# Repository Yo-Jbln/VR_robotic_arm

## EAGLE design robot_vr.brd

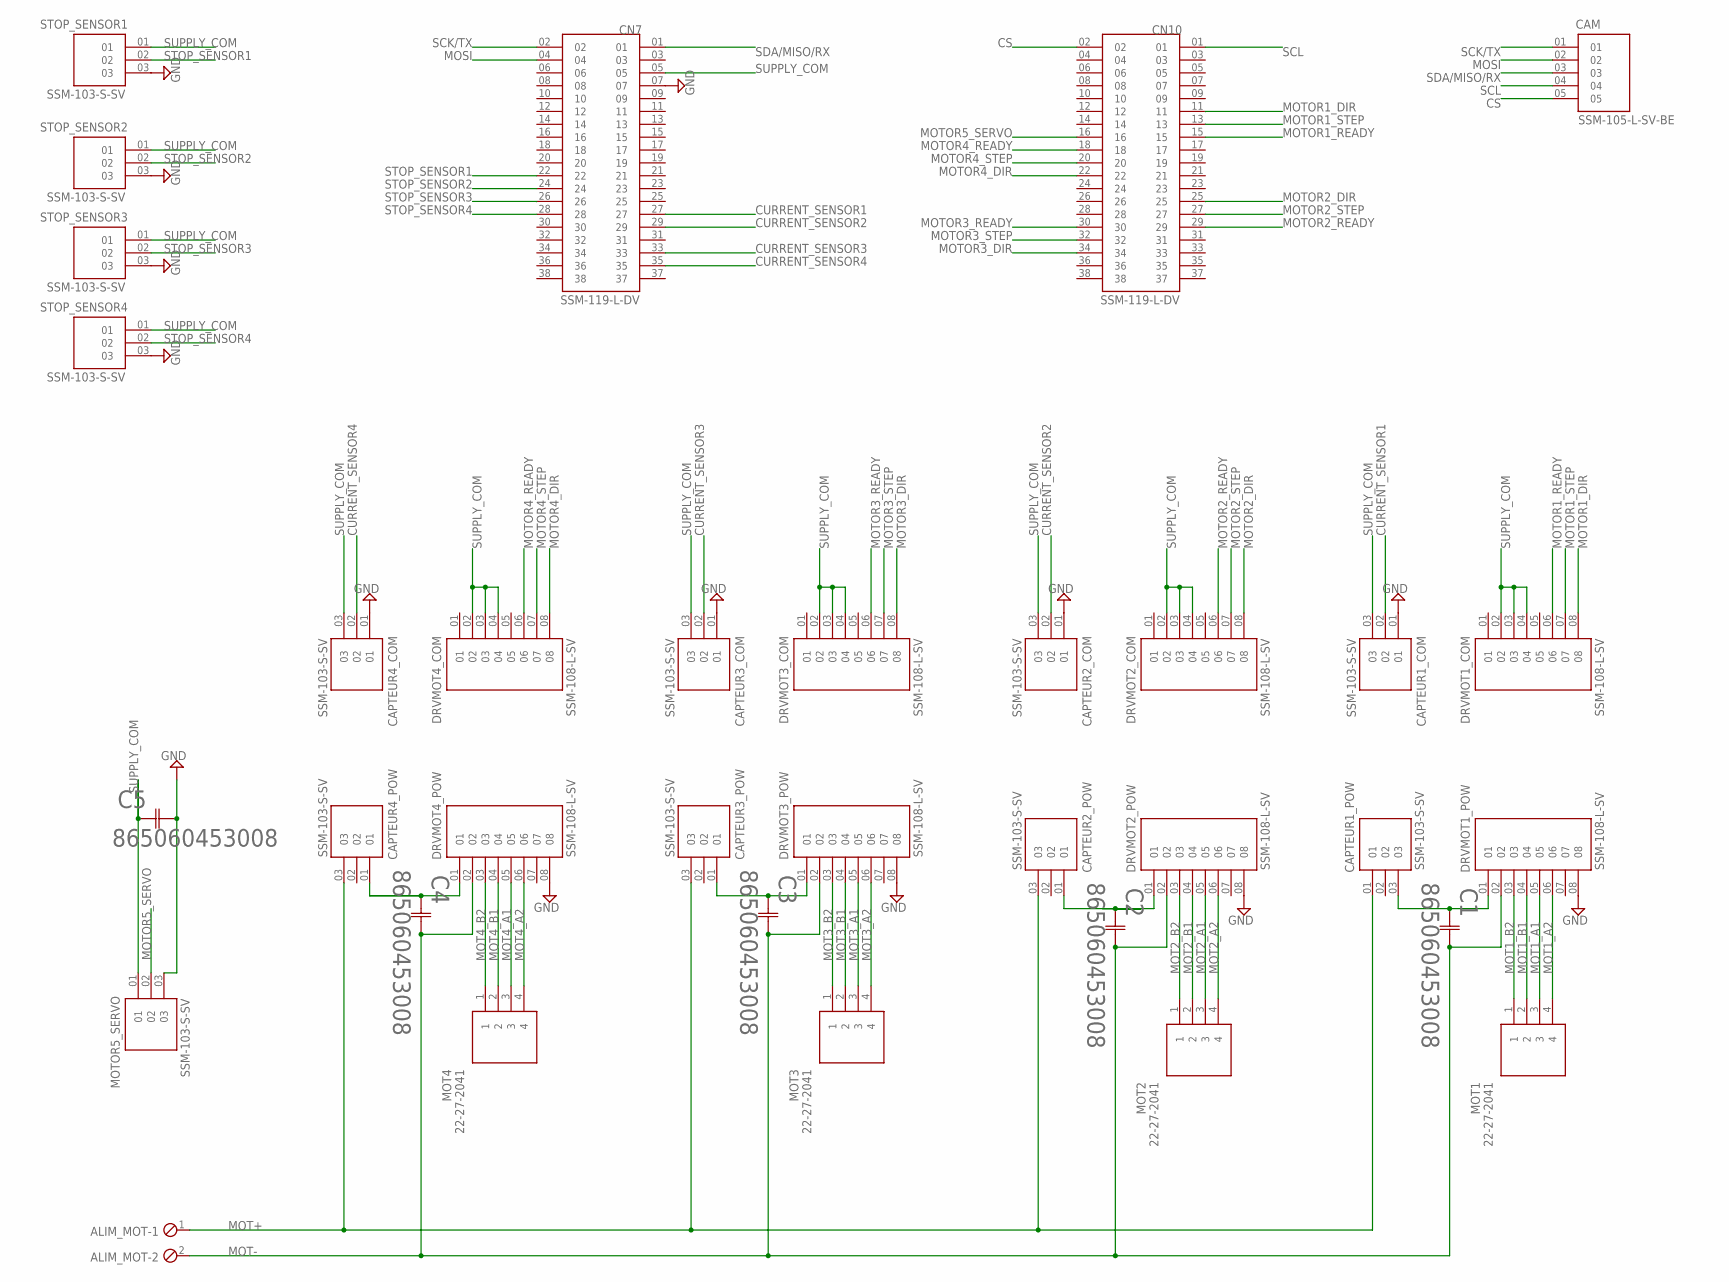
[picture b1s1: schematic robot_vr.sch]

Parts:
ALIM_MOT: MPT2; 2POL254
C1, C2, C3, C4, C5: 865060453008; CAP_865060453008_WRE
CAM: SSM-105-L-SV-BE; SAMTEC_SSM-105-L-SV-BE
CAPTEUR1_COM, CAPTEUR1_POW, CAPTEUR2_COM, CAPTEUR2_POW, CAPTEUR3_COM, CAPTEUR3_POW, CAPTEUR4_COM, CAPTEUR4_POW: SSM-103-S-SV; SAMTEC_SSM-103-S-SV
CN7, CN10: SSM-119-L-DV; SAMTEC_SSM-119-L-DV
DRVMOT1_COM, DRVMOT1_POW, DRVMOT2_COM, DRVMOT2_POW, DRVMOT3_COM, DRVMOT3_POW, DRVMOT4_COM, DRVMOT4_POW: SSM-108-L-SV; SAMTEC_SSM-108-L-SV
MOT1, MOT2, MOT3, MOT4: 22-27-2041; HDRV4W64P254_100_4X1_1016X580H
MOTOR5_SERVO: SSM-103-S-SV; SAMTEC_SSM-103-S-SV
STOP_SENSOR1, STOP_SENSOR2, STOP_SENSOR3, STOP_SENSOR4: SSM-103-S-SV; SAMTEC_SSM-103-S-SV

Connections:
CAPTEUR_MOT1: C1.1, CAPTEUR1_POW.03, DRVMOT1_POW.01
CAPTEUR_MOT2: C2.1, CAPTEUR2_POW.01, DRVMOT2_POW.01
CAPTEUR_MOT3: C3.1, CAPTEUR3_POW.01, DRVMOT3_POW.01
CAPTEUR_MOT4: C4.1, CAPTEUR4_POW.01, DRVMOT4_POW.01
CS: CAM.05, CN10.02
CURRENT_SENSOR1: CAPTEUR1_COM.02, CN7.27
CURRENT_SENSOR2: CAPTEUR2_COM.02, CN7.29
CURRENT_SENSOR3: CAPTEUR3_COM.02, CN7.33
CURRENT_SENSOR4: CAPTEUR4_COM.02, CN7.35
GND: C5.2, CAPTEUR1_COM.01, CAPTEUR2_COM.01, CAPTEUR3_COM.01, CAPTEUR4_COM.01, CN7.07, DRVMOT1_POW.08, DRVMOT2_POW.08, DRVMOT3_POW.08, DRVMOT4_POW.08, MOTOR5_SERVO.03, STOP_SENSOR1.03, STOP_SENSOR2.03, STOP_SENSOR3.03, STOP_SENSOR4.03
MOSI: CAM.02, CN7.04
MOT1_A1: DRVMOT1_POW.05, MOT1.3
MOT1_A2: DRVMOT1_POW.06, MOT1.4
MOT1_B1: DRVMOT1_POW.04, MOT1.2
MOT1_B2: DRVMOT1_POW.03, MOT1.1
MOT2_A1: DRVMOT2_POW.05, MOT2.3
MOT2_A2: DRVMOT2_POW.06, MOT2.4
MOT2_B1: DRVMOT2_POW.04, MOT2.2
MOT2_B2: DRVMOT2_POW.03, MOT2.1
MOT3_A1: DRVMOT3_POW.05, MOT3.3
MOT3_A2: DRVMOT3_POW.06, MOT3.4
MOT3_B1: DRVMOT3_POW.04, MOT3.2
MOT3_B2: DRVMOT3_POW.03, MOT3.1
MOT4_A1: DRVMOT4_POW.05, MOT4.3
MOT4_A2: DRVMOT4_POW.06, MOT4.4
MOT4_B1: DRVMOT4_POW.04, MOT4.2
MOT4_B2: DRVMOT4_POW.03, MOT4.1
MOT+: ALIM_MOT.1, CAPTEUR1_POW.01, CAPTEUR2_POW.03, CAPTEUR3_POW.03, CAPTEUR4_POW.03
MOT-: ALIM_MOT.2, C1.2, C2.2, C3.2, C4.2, DRVMOT1_POW.02, DRVMOT2_POW.02, DRVMOT3_POW.02, DRVMOT4_POW.02
MOTOR1_DIR: CN10.11, DRVMOT1_COM.08
MOTOR1_READY: CN10.15, DRVMOT1_COM.06
MOTOR1_STEP: CN10.13, DRVMOT1_COM.07
MOTOR2_DIR: CN10.25, DRVMOT2_COM.08
MOTOR2_READY: CN10.29, DRVMOT2_COM.06
MOTOR2_STEP: CN10.27, DRVMOT2_COM.07
MOTOR3_DIR: CN10.34, DRVMOT3_COM.08
MOTOR3_READY: CN10.30, DRVMOT3_COM.06
MOTOR3_STEP: CN10.32, DRVMOT3_COM.07
MOTOR4_DIR: CN10.22, DRVMOT4_COM.08
MOTOR4_READY: CN10.18, DRVMOT4_COM.06
MOTOR4_STEP: CN10.20, DRVMOT4_COM.07
MOTOR5_SERVO: CN10.16, MOTOR5_SERVO.02
SCK/TX: CAM.01, CN7.02
SCL: CAM.04, CN10.01
SDA/MISO/RX: CAM.03, CN7.01
STOP_SENSOR1: CN7.22, STOP_SENSOR1.02
STOP_SENSOR2: CN7.24, STOP_SENSOR2.02
STOP_SENSOR3: CN7.26, STOP_SENSOR3.02
STOP_SENSOR4: CN7.28, STOP_SENSOR4.02
SUPPLY_COM: C5.1, CAPTEUR1_COM.03, CAPTEUR2_COM.03, CAPTEUR3_COM.03, CAPTEUR4_COM.03, CN7.05, DRVMOT1_COM.02, DRVMOT1_COM.03, DRVMOT1_COM.04, DRVMOT2_COM.02, DRVMOT2_COM.03, DRVMOT2_COM.04, DRVMOT3_COM.02, DRVMOT3_COM.03, DRVMOT3_COM.04, DRVMOT4_COM.02, DRVMOT4_COM.03, DRVMOT4_COM.04, MOTOR5_SERVO.01, STOP_SENSOR1.01, STOP_SENSOR2.01, STOP_SENSOR3.01, STOP_SENSOR4.01

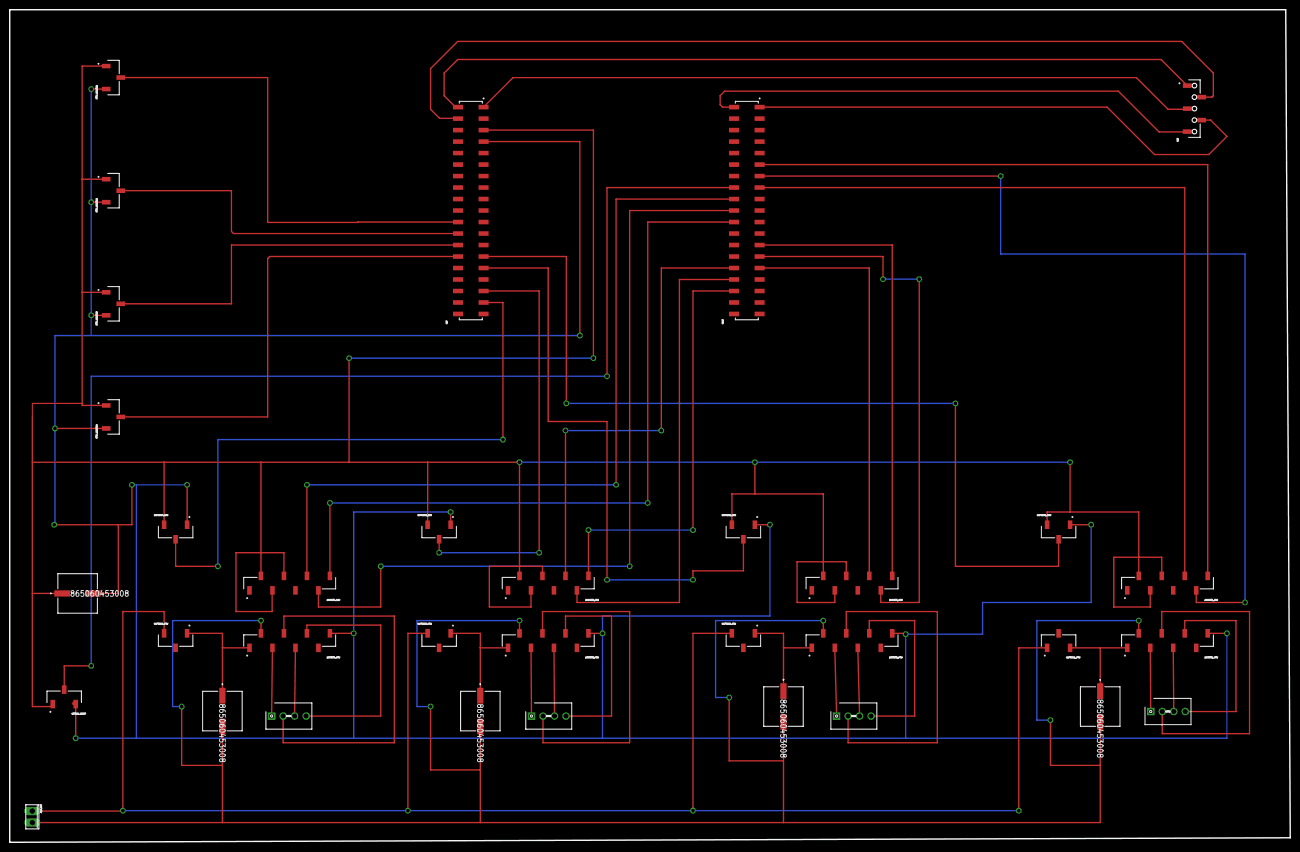
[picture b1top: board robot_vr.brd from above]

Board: 2 copper layers, 283.0 x 184.0 mm, 34 parts (0 on the bottom side), 50 nets.

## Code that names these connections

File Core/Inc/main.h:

/* USER CODE BEGIN Header */
/**
  ******************************************************************************
  * @file           : main.h
  * @brief          : Header for main.c file.
  *                   This file contains the common defines of the application.
  ******************************************************************************
  * @attention
  *
  * <h2><center>&copy; Copyright (c) 2021 STMicroelectronics.
  * All rights reserved.</center></h2>
  *
  * This software component is licensed by ST under BSD 3-Clause license,
  * the "License"; You may not use this file except in compliance with the
  * License. You may obtain a copy of the License at:
  *                        opensource.org/licenses/BSD-3-Clause
  *
  ******************************************************************************
  */
/* USER CODE END Header */

/* Define to prevent recursive inclusion -------------------------------------*/
#ifndef __MAIN_H
#define __MAIN_H

#ifdef __cplusplus
extern "C" {
#endif

/* Includes ------------------------------------------------------------------*/
#include "stm32g4xx_hal.h"

/* Private includes ----------------------------------------------------------*/
/* USER CODE BEGIN Includes */
#include "math.h"
#include "stdio.h"
#include "stdlib.h"
#include "console.h"
/* USER CODE END Includes */

/* Exported types ------------------------------------------------------------*/
/* USER CODE BEGIN ET */

/* USER CODE END ET */

/* Exported constants --------------------------------------------------------*/
/* USER CODE BEGIN EC */

/* USER CODE END EC */

/* Exported macro ------------------------------------------------------------*/
/* USER CODE BEGIN EM */
extern UART_HandleTypeDef huart2;
/* USER CODE END EM */

void HAL_TIM_MspPostInit(TIM_HandleTypeDef *htim);

/* Exported functions prototypes ---------------------------------------------*/
void Error_Handler(void);

/* USER CODE BEGIN EFP */
/* USER CODE END EFP */

/* Private defines -----------------------------------------------------------*/
#define Stop_Sensor2_Pin GPIO_PIN_13
#define Stop_Sensor2_GPIO_Port GPIOC
#define Stop_Sensor2_EXTI_IRQn EXTI15_10_IRQn
#define Stop_Sensor3_Pin GPIO_PIN_14
#define Stop_Sensor3_GPIO_Port GPIOC
#define Stop_Sensor3_EXTI_IRQn EXTI15_10_IRQn
#define Stop_Sensor4_Pin GPIO_PIN_15
#define Stop_Sensor4_GPIO_Port GPIOC
#define Stop_Sensor4_EXTI_IRQn EXTI15_10_IRQn
#define Current_Sensor4_Pin GPIO_PIN_1
#define Current_Sensor4_GPIO_Port GPIOC
#define Current_Sensor1_Pin GPIO_PIN_0
#define Current_Sensor1_GPIO_Port GPIOA
#define Current_Sensor2_Pin GPIO_PIN_1
#define Current_Sensor2_GPIO_Port GPIOA
#define Current_Sensor3_Pin GPIO_PIN_0
#define Current_Sensor3_GPIO_Port GPIOB
#define Motor1_Ready_Pin GPIO_PIN_12
#define Motor1_Ready_GPIO_Port GPIOB
#define Motor2_Ready_Pin GPIO_PIN_13
#define Motor2_Ready_GPIO_Port GPIOB
#define Motor2_DIR_Pin GPIO_PIN_15
#define Motor2_DIR_GPIO_Port GPIOB
#define Motor4_DIR_Pin GPIO_PIN_9
#define Motor4_DIR_GPIO_Port GPIOA
#define Motor3_DIR_Pin GPIO_PIN_10
#define Motor3_DIR_GPIO_Port GPIOA
#define Motor1_DIR_Pin GPIO_PIN_12
#define Motor1_DIR_GPIO_Port GPIOA
#define Motor3_Ready_Pin GPIO_PIN_5
#define Motor3_Ready_GPIO_Port GPIOB
#define Motor4_Ready_Pin GPIO_PIN_6
#define Motor4_Ready_GPIO_Port GPIOB
#define Stop_Sensor1_Pin GPIO_PIN_7
#define Stop_Sensor1_GPIO_Port GPIOB
#define Stop_Sensor1_EXTI_IRQn EXTI9_5_IRQn
/* USER CODE BEGIN Private defines */

/* USER CODE END Private defines */

#ifdef __cplusplus
}
#endif

#endif /* __MAIN_H */

/************************ (C) COPYRIGHT STMicroelectronics *****END OF FILE****/

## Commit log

2021-12-14 Create PCB

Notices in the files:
parts and their libraries:
COPYRIGHT: Copyright (C) 2022 Ultra Librarian. All rights reserved.
